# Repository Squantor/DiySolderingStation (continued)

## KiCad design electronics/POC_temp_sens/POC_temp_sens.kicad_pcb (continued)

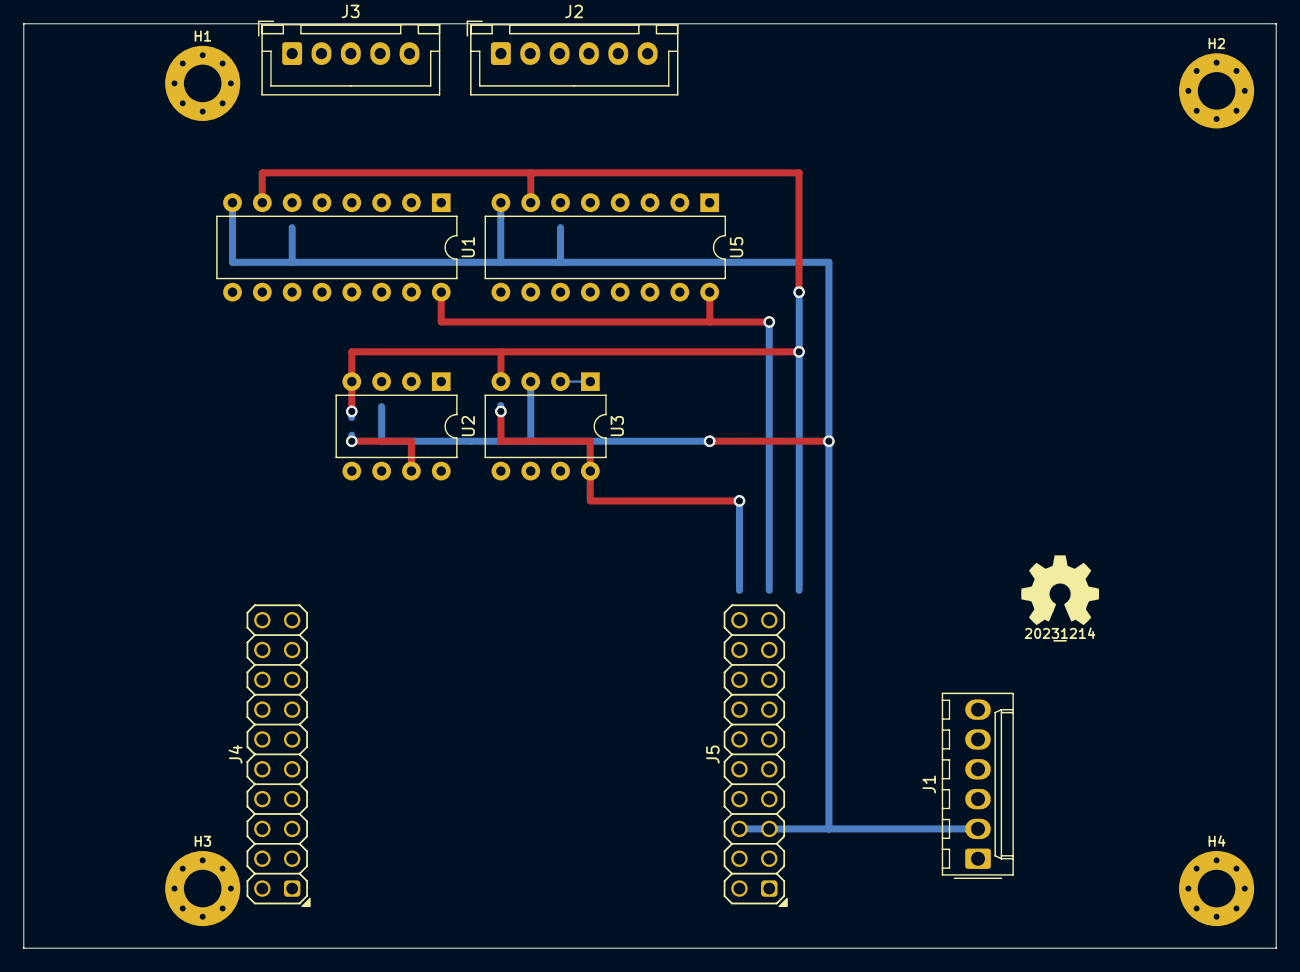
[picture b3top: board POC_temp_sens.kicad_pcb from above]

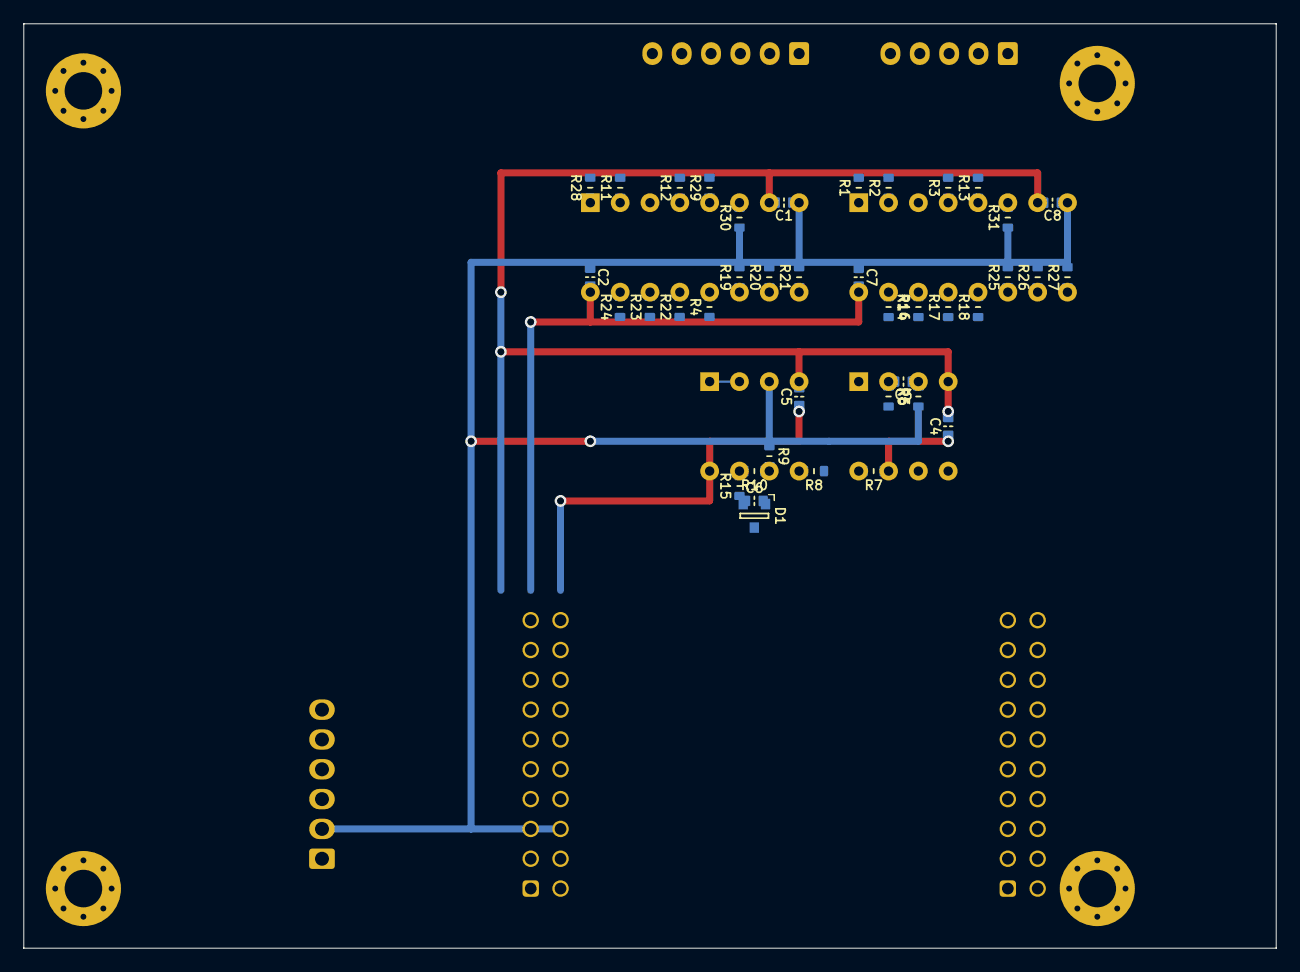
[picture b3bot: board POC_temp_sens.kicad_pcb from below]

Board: 2 copper layers, 106.7 x 78.7 mm, 55 parts (40 on the bottom side), 44 nets.

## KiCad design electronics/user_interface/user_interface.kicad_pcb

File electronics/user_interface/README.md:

# DIY soldering station user interface
User interface for the DIY soldering station consisting of a 2 by 16 character LCD and 4 buttons with a rotary encoder.
## TODO's
* schematic entry
* PCB layout
* Review with one night in between
* Produce at
* Assemble
* Test & characterise
* update Readme.md with pictures and BOM

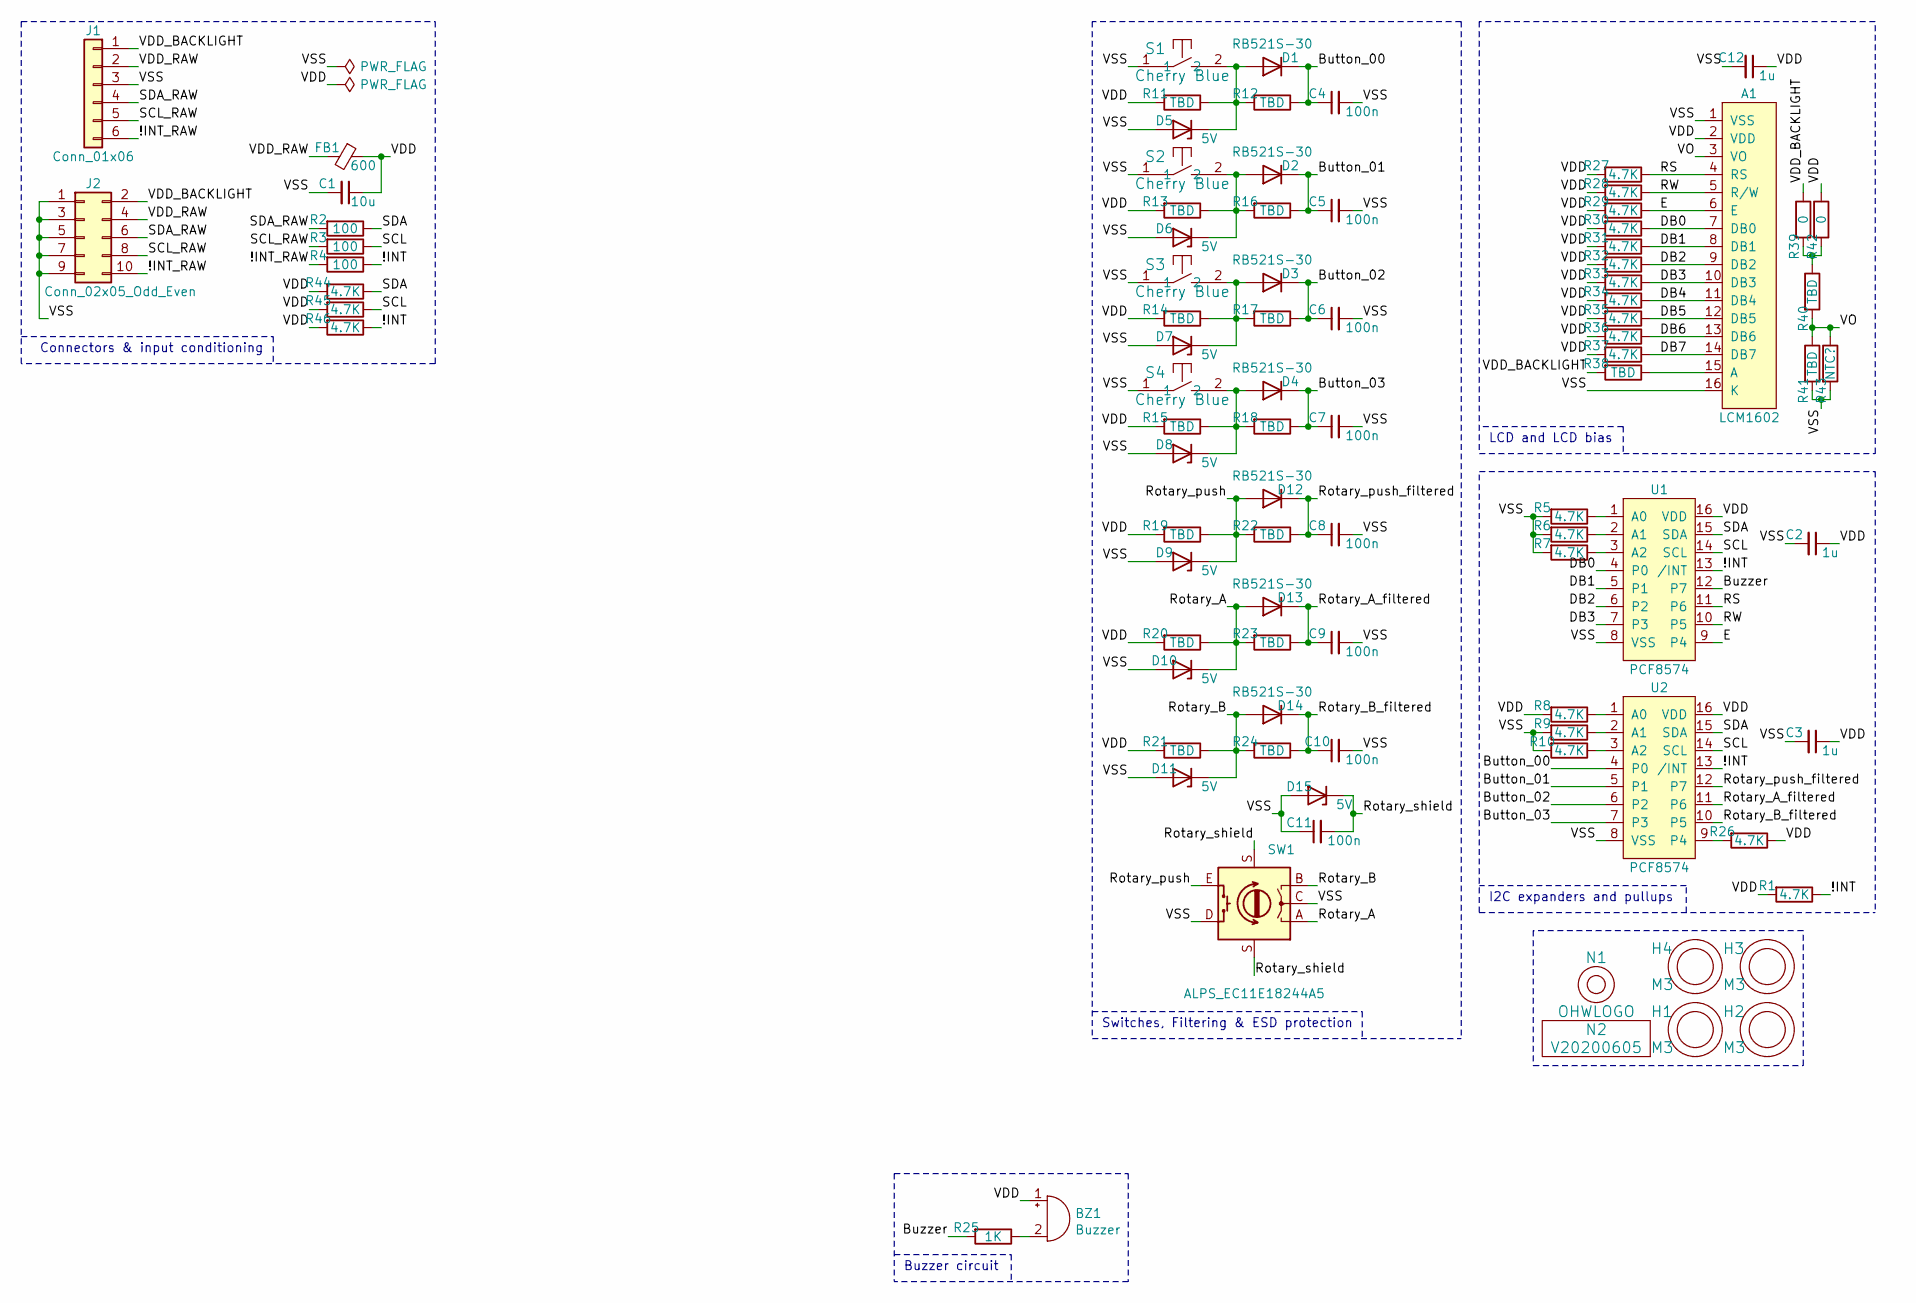
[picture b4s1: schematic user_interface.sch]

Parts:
A1: LCM1602; LCM1602K
BZ1: Buzzer; Buzzer_12x9.5RM7.6
C1: 10u; C_0603
C2, C3, C12: 1u; C_0603
C4, C5, C6, C7, C8, C9, C10, C11: 100n; C_0603
D1, D2, D3, D4, D12, D13, D14: RB521S-30; SOD-523
D5, D6, D7, D8, D9, D10, D11, D15: 5V; SOD-523
FB1: 600; L_0603
H1, H2, H3, H4: M3; MountingHole_3.2mm_M3_Pad_Via
J1: Conn_01x06; JST_PH_S6B-PH-K_1x06_P2.00mm_Horizontal
J2: Conn_02x05_Odd_Even; Header-0254-2X05-H010
N1: OHWLOGO; OSHW-Symbol_6.7x6mm_SilkScreen
N2: V20200605; Label_Generic
R1, R5, R6, R7, R8, R9, R10, R26, R27, R28, R29, R30, R31, R32, R33, R34, R35, R36, R37, R44, R45, R46: 4.7K; R_0603_hand
R2, R3, R4: 100; R_0603_hand
R11, R12, R13, R14, R15, R16, R17, R18, R19, R20, R21, R22, R23, R24, R38, R40, R41: TBD; R_0603_hand
R25: 1K; R_0603_hand
R39, R42: 0; R_0603_hand
R43: NTC?; R_0603_hand
S1, S2, S3, S4: Cherry Blue; MXOnly-1U-NoLED
SW1: ALPS_EC11E18244A5; ALPS_EC11E_style5
U1, U2: PCF8574; SOT162-1-NXP

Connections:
/!INT: R1.1, R4.1, R46.1, U1.13 (/INT), U2.13 (/INT)
/!INT_RAW: J1.6, J2.10, R4.2
/Button_00: C4.1, D1.1 (K), R12.1, U2.4 (P0)
/Button_01: C5.1, D2.1 (K), R16.1, U2.5 (P1)
/Button_02: C6.1, D3.1 (K), R17.1, U2.6 (P2)
/Button_03: C7.1, D4.1 (K), R18.1, U2.7 (P3)
/Buzzer: R25.2, U1.12 (P7)
/DB0: A1.7 (DB0), R30.1, U1.4 (P0)
/DB1: A1.8 (DB1), R31.1, U1.5 (P1)
/DB2: A1.9 (DB2), R32.1, U1.6 (P2)
/DB3: A1.10 (DB3), R33.1, U1.7 (P3)
/DB4: A1.11 (DB4), R34.1
/DB5: A1.12 (DB5), R35.1
/DB6: A1.13 (DB6), R36.1
/DB7: A1.14 (DB7), R37.1
/E: A1.6 (E), R29.1, U1.9 (P4)
/RS: A1.4 (RS), R27.1, U1.11 (P6)
/RW: A1.5 (R/W), R28.1, U1.10 (P5)
/Rotary_A: D10.1 (K), D13.2 (A), R20.1, R23.2, SW1.A
/Rotary_A_filtered: C9.1, D13.1 (K), R23.1, U2.11 (P6)
/Rotary_B: D11.1 (K), D14.2 (A), R21.1, R24.2, SW1.B
/Rotary_B_filtered: C10.1, D14.1 (K), R24.1, U2.10 (P5)
/Rotary_push: D9.1 (K), D12.2 (A), R19.1, R22.2, SW1.E
/Rotary_push_filtered: C8.1, D12.1 (K), R22.1, U2.12 (P7)
/Rotary_shield: C11.2, D15.1 (K), SW1.S (Shield)
/SCL: R3.1, R45.1, U1.14 (SCL), U2.14 (SCL)
/SCL_RAW: J1.5, J2.8, R3.2
/SDA: R2.1, R44.1, U1.15 (SDA), U2.15 (SDA)
/SDA_RAW: J1.4, J2.6, R2.2
/VDD: A1.2 (VDD), BZ1.1 (-), C1.1, C2.1, C3.1, C12.1, FB1.1, R1.2, R8.2, R11.2, R13.2, R14.2, R15.2, R19.2, R20.2, R21.2, R26.1, R27.2, R28.2, R29.2, R30.2, R31.2, R32.2, R33.2, R34.2, R35.2, R36.2, R37.2, R42.1, R44.2, R45.2, R46.2, U1.16 (VDD), U2.16 (VDD)
/VDD_BACKLIGHT: J1.1, J2.2, R38.2, R39.1
/VDD_RAW: FB1.2, J1.2, J2.4
/VO: A1.3 (VO), R40.2, R41.1, R43.1
/VSS: A1.1 (VSS), A1.16 (K), C1.2, C2.2, C3.2, C4.2, C5.2, C6.2, C7.2, C8.2, C9.2, C10.2, C11.1, C12.2, D5.2 (A), D6.2 (A), D7.2 (A), D8.2 (A), D9.2 (A), D10.2 (A), D11.2 (A), D15.2 (A), J1.3, J2.1, J2.3, J2.5, J2.7, J2.9, R5.2, R6.2, R7.2, R9.2, R10.2, R41.2, R43.2, S1.1, S2.1, S3.1, S4.1, SW1.C, SW1.D, U1.8 (VSS), U2.8 (VSS)
unnamed: A1.15 (A), R38.1
unnamed: BZ1.2 (+), R25.1
unnamed: D1.2 (A), D5.1 (K), R11.1, R12.2, S1.2
unnamed: D2.2 (A), D6.1 (K), R13.1, R16.2, S2.2
unnamed: D3.2 (A), D7.1 (K), R14.1, R17.2, S3.2
unnamed: D4.2 (A), D8.1 (K), R15.1, R18.2, S4.2
unnamed: R5.1, U1.1 (A0)
unnamed: R6.1, U1.2 (A1)
unnamed: R7.1, U1.3 (A2)
unnamed: R8.1, U2.1 (A0)
unnamed: R9.1, U2.2 (A1)
unnamed: R10.1, U2.3 (A2)
unnamed: R26.2, U2.9 (P4)
unnamed: R39.2, R40.1, R42.2

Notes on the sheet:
LCD and LCD bias
I2C expanders and pullups
Switches, Filtering & ESD protection
Connectors & input conditioning
Buzzer circuit

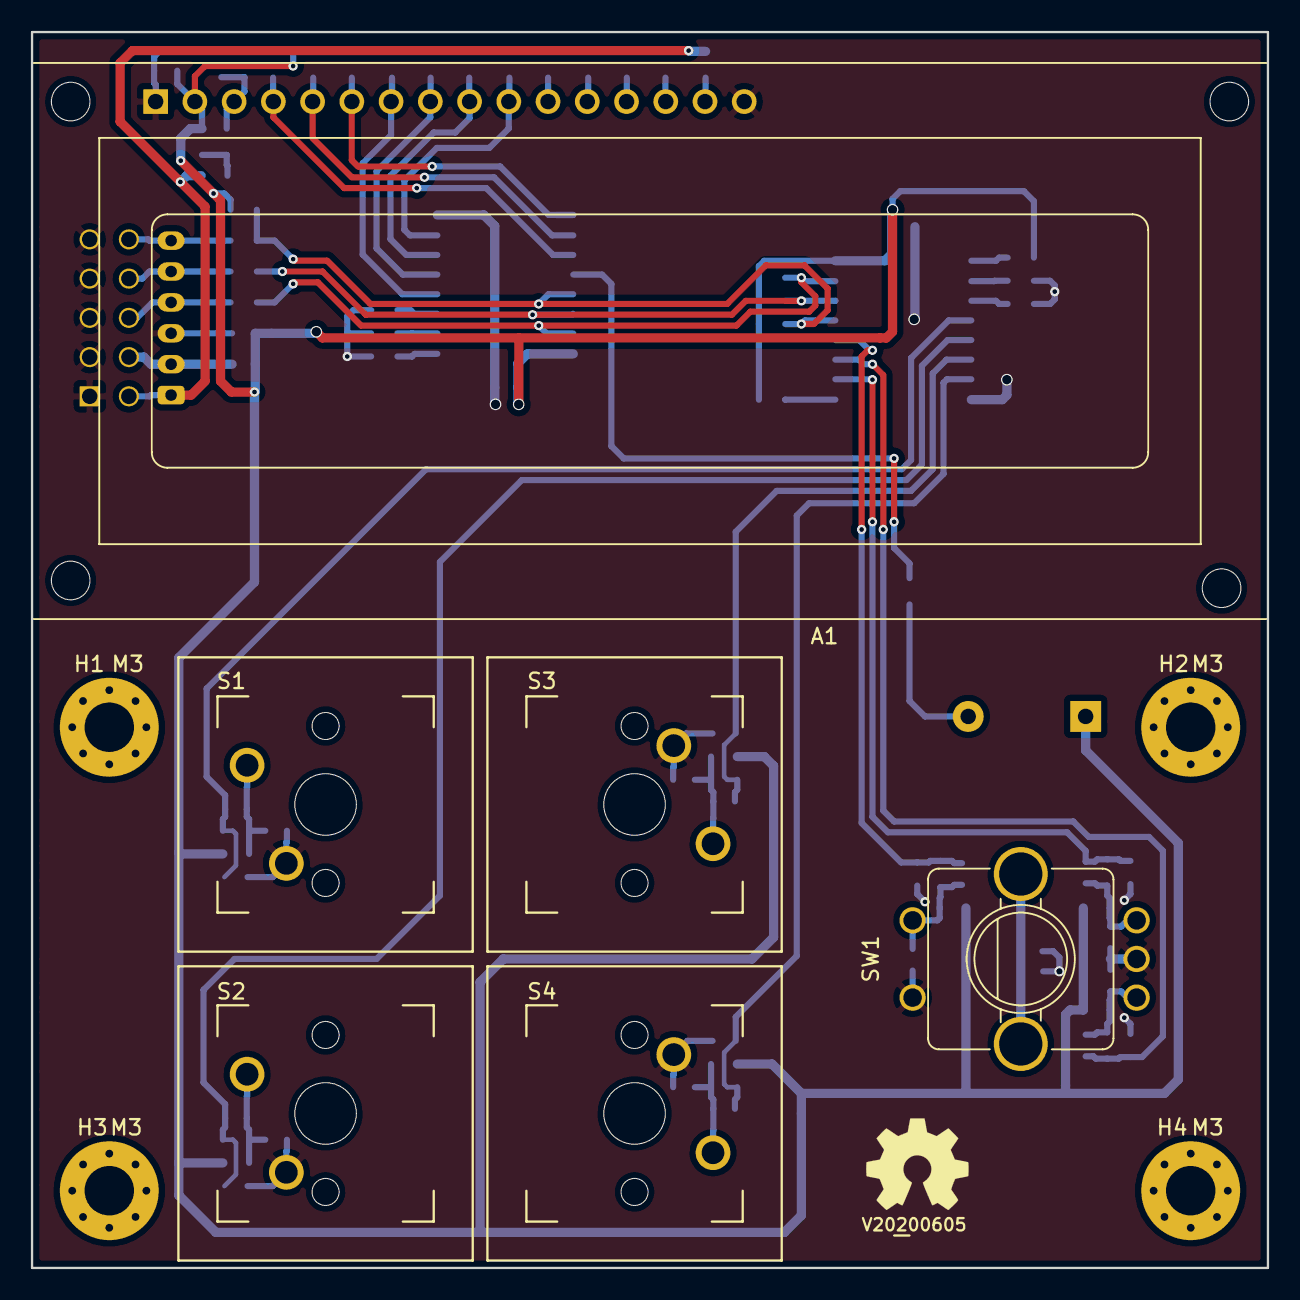
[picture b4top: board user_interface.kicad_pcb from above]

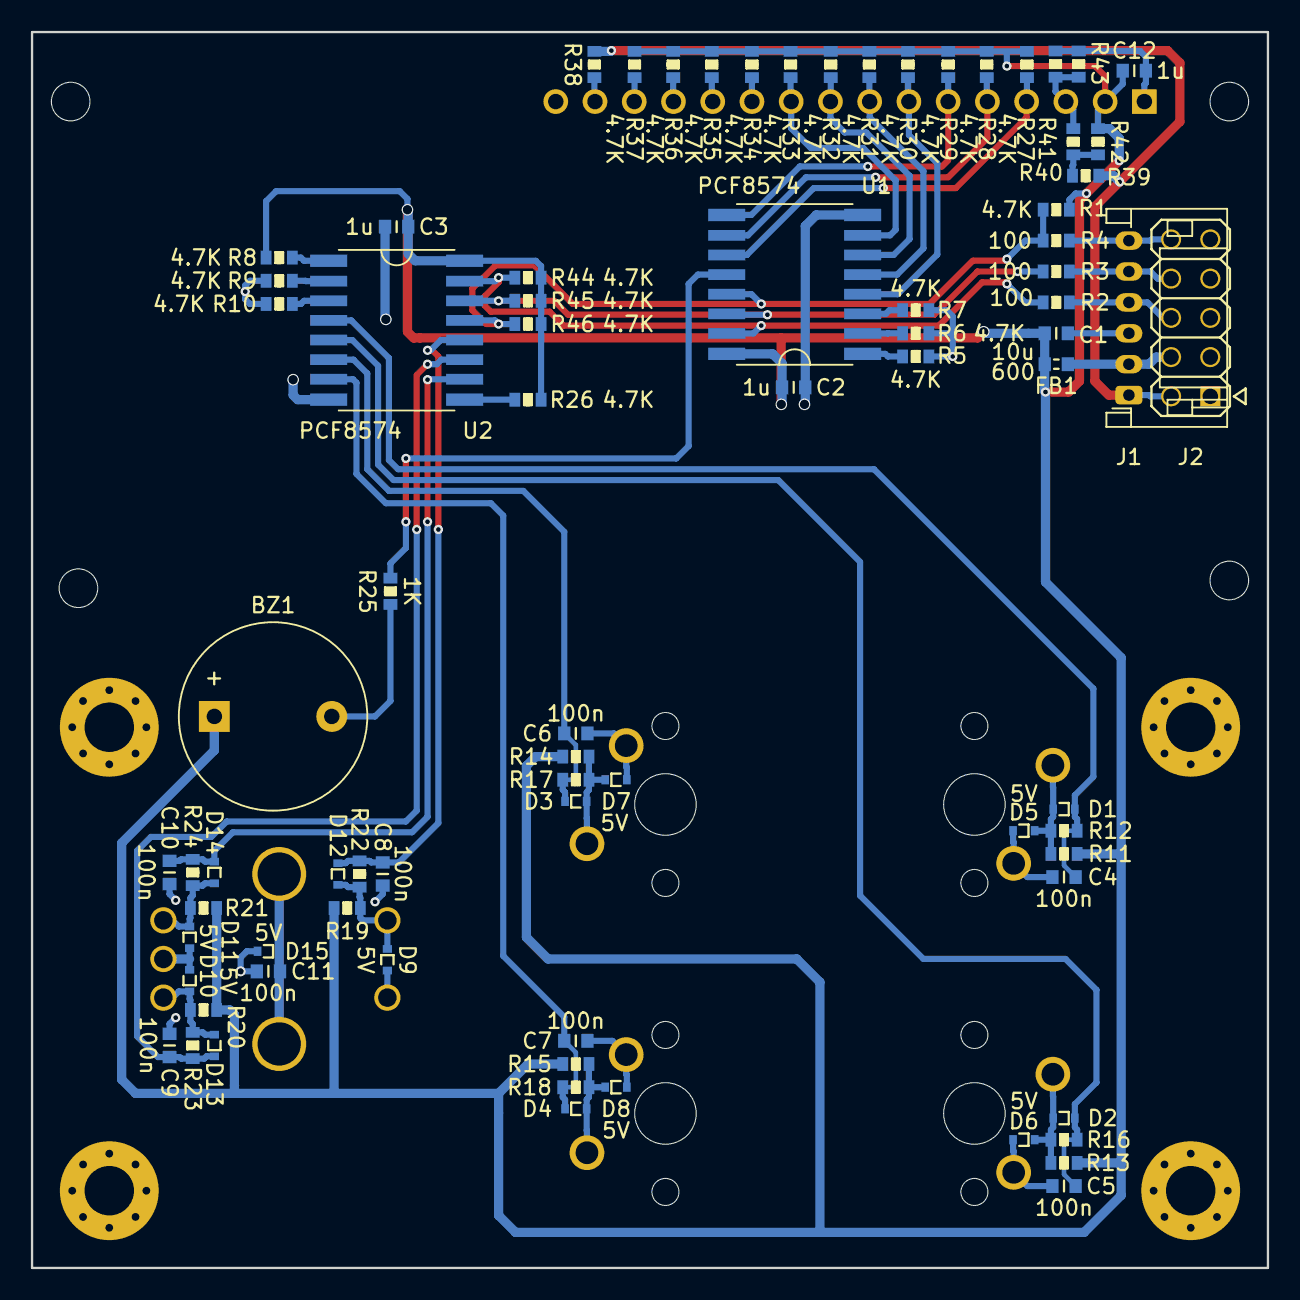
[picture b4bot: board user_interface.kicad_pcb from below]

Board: 2 copper layers, 80.0 x 80.0 mm, 91 parts (79 on the bottom side), 48 nets.

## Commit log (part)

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2020-05-04 typo
2020-05-04 copied over libmcull uart demo project here
2020-05-04 imported a simple time delay library
2020-05-05 split the C bits from the time_delay
2020-05-05 added warning if you did not define a setting
2020-05-05 lets make a delaying class
2020-05-05 updated date on copyright
2020-05-05 added boilerplate stuff
2020-05-05 refactored the systick global increment value
2020-05-05 WIP delay class
2020-05-05 using delay class
2020-05-05 switched to newer C standard
2020-05-05 added time interval class files
2020-05-05 made member const
2020-05-05 added time interval class
2020-05-05 refactored name
2020-05-05 switched to non blocking interval for demo print
2020-05-05 faster builds please
2020-05-06 defined input pin of the zero crossing detector
2020-05-06 started with interrupts on zerocross detector
2020-05-06 working zerocross detection interrupt
2020-05-06 added zerocross counter, seems a bit glitchy...
2020-05-06 enabled hysteresis on pin, much less glitches
2020-05-06 added initial SCR/SSR control scheme
2020-05-07 added SSR control pin
2020-05-07 SSR control demo
2020-05-11 starting with PDM generator
2020-05-11 switched over demo code to separate class
2020-05-11 templated the PDM generator
2020-05-11 added initial projects for the power control and user interface
2020-05-11 added electronics page overview
2020-05-12 processed review comments
2020-05-12 added PCB component library
2020-05-12 added switch library from ai03-2725
2020-05-12 started with user interface schematic entry
2020-05-12 added switch library to user interface project
2020-05-14 power input circuit
2020-05-14 board outline, input circuit layout
2020-05-14 newer PCB library
2020-05-14 ignoring autosave files
2020-05-14 added NXP footprint
2020-05-14 footprints assignment, minor layout positioning
2020-05-14 updated date
2020-05-15 added mounting holes, some silk moves
2020-05-15 minor schematic updates
2020-05-16 added initial switch schematic
2020-05-16 added 3 switches extra to schematic
2020-05-16 minor silk and layout
2020-05-16 added ESD protection
2020-05-16 updated pcb library, included switch libraries
2020-05-16 assigned names to diodes
2020-05-16 rotary encoder now available
2020-05-16 rotary encoder added to schematic WIP components and debouncing
2020-05-16 added rotary encoder knob to PCB
2020-05-17 LCD module now available
2020-05-17 Added LCD, connections to expander and LCD bias circuit
2020-05-17 imported LCD parts, changed board size
2020-05-17 beautified schematic a bit, passes ERC
2020-05-17 mechanical components placed, initial placing of passives
2020-05-17 cache updates
2020-05-19 component placement
2020-05-20 updated footprints to include 3dmodel of SOD-523 diode
2020-05-21 WIP routing of filtering on the buttons
2020-05-21 WIP switch filtering placement and routing, silk changes
2020-05-21 updated versionnumber
2020-05-21 silk placement on filtering done
2020-05-21 WIP LCD parts layout, silk placement, locking UI components (LCD, buttons, etc)
2020-05-21 small updates
2020-05-22 some routing
2020-05-22 added pullup resistors, updated versionnumber
2020-05-22 routing completed
2020-05-22 silk updates
2020-05-24 updated versionnumber, changed address selection tracks so you could disconnect them by cutting traces
2020-05-24 updated to newer cherry mx footprint, changed silk screen of those keys
2020-06-02 added buzzer circuit
2020-06-05 prettyfied the buzzer circuit
2020-06-05 layed out buzzer circuit
2020-06-05 minor silk shifts
2020-06-05 minor silk changes
2024-06-28 updated PCB library
2024-06-28 modifications to newer project structure
2024-06-29 added C14 inlet cutout template and clip
2024-06-30 added wider flange for putting it in case
2024-07-19 added test connector plate for JBC T245 and T115 handle connectors
2024-07-24 added reverse engineered CD-2BC station, going to use some parts from this schematic in this station
2024-07-24 initial start of a CD-2BC T245 thermocouple sensing circuit
2024-07-24 WIP placement
2024-07-24 switched to dual mux for experiments
2024-07-25 switched mux pinning and additional placing
2024-08-02 changed submodule path
2024-08-02 protoboard is now 1 on 1 copy of real protoboard
2024-08-03 reworked firmware structure
2024-08-03 updated mechanical bits documentation
2024-08-03 added more info on mechanical bits
2024-08-04 renaming project and adding some HSI documentation to POC temp sens
2024-08-04 renaming firmware temperature sensing POC
2024-08-04 added unittests
2024-08-04 added application, added systick
2024-08-04 gotten UART loopback working
2024-08-04 started with asynchronous uart hal
2024-08-05 started with synchronous interrupt driven UART HAL
2024-08-05 WIP synchronous interrupt driven UART HAL
2024-08-07 copied ringbuffer to move to libmcu eventually
2024-08-23 uart hal transmit with interrupts work
2024-08-23 added vs code config file garbage
2024-08-23 receive works
2024-08-23 print style functions
2024-08-23 using variadic templates
2024-08-23 added more resistors to multiplexers
2024-08-30 starting with simple commandline
2024-08-30 ported over ansi parser
2024-08-30 added ansi cursor command tests
2024-08-30 starting with creating simple commandline
2024-09-06 method name refactoring
2024-09-06 simple console driver
2024-09-06 console overflow test
2024-09-06 WIP commandline handler
2024-09-06 changed cr/lf handling in commandline, added commandline to POC temp sensing
2024-09-13 initial creation of a simple command handler
2024-09-13 added help function
2024-09-13 started with a command value stack interpreter
2024-09-13 moved ringbuffer to squlib, libmcu will get its own private one
2024-09-13 added some TODO's
2024-09-13 added few common forth primitives, started with parsing a number
2024-09-13 added ascii parsing push
2024-09-13 integrated command interpreter
2024-09-13 refactored result name into results
2024-09-13 split out command handlers
2024-09-13 forwarding numbers to stack
2024-09-13 added additional commands for stack handling
2024-09-13 refactored value stack, fixed command interpreter tests
2024-09-13 fixed negative number handling, added decimal print
2024-09-14 updated HSI with multiplexer pins, power detection pin and ADC sensing pin
2024-09-14 Added number input to help
2024-09-14 merging sparse headers together
2024-09-14 added application state with status command
2024-09-14 properly detects power state
2024-09-16 refactoring by moving some things to libMcu
2024-09-20 separating out buffered and unbuffered console drivers
2024-09-20 WIP merging print into console drivers
2024-09-20 merged print functionality into console
2024-09-20 preparing to convert toascii from struct/class to function templates
2024-09-20 turned toascii into functions
2024-09-20 converted to console.print
2024-09-21 small changes, updated HSI
2024-09-22 added some setting
2024-09-22 started with multiplexer command
2024-09-26 completed multiplexer set command
2024-09-26 updated library bugfix
2024-09-26 updates due to namespace refactoring
2024-09-27 libmcu namespace renames
2024-09-27 ADC works
2024-09-27 added TC readout command
2024-09-28 started with POC temperature control
2024-09-29 added digital supplies and P&R
2024-09-29 added analog powersupply
2024-09-29 added analog supplies, started with nuclone addition
2024-09-30 added nuclone footprint and component
2024-10-02 analog input filtering and post amps, started with diff amps
2024-10-07 synchronized with project template
2024-10-07 finished diff amp schematic and analog multiplexers
2024-10-11 WIP DIY soldering station
2024-10-18 updated to use clocking API
2024-10-25 placed, duplicated power stage
2024-10-25 straggling changes
2024-10-25 added zerocross detector schematic
2024-11-11 replaced current sense resistor, imported zerocross detector
2024-11-15 more schematic bits added, passes ERC, placing components and fixing silk orientations
2024-11-29 some placing and routing done
2024-12-13 further work on place and route, fixed some things with schematic
2025-04-11 WIP further routing
2025-04-18 WIP silk placement
2025-05-02 ignoring some outputs
2025-05-02 updated silk placements and component values
2025-05-04 updated silk placement
2025-05-10 added values to all components
2025-05-13 preparing for production
2025-07-25 builds with newer version of libmcu
2025-07-29 changed/updated component values
2025-08-19 fixing build errors after libmcu update
2025-09-05 porting to newer libcmu API completed
2025-09-05 Updated PCB/Schematic to kicad 9
2025-09-08 Added zerocross detection pin and refactored pin/port/function names to adhere to naming convention
2025-09-08 WIP zero cross detector
2025-09-08 working zero cross interrupt pin
2025-09-09 some refactoring of application object names
2025-09-10 refactoring some names and added zerocrossing class
2025-09-10 added power control pins and functions
2025-09-26 updated library for iocon glitch filter settings, added glitch filtering to Zerocross detector pin
2025-09-26 Initial commit for dual powerstage module
2025-09-26 Schematic and layout done, review needed
2025-10-03 Review completed, fixed DRC warnings
2025-10-03 Started by adding the SH1106 display
2025-10-07 fixed issues with dependency generation
2025-10-10 working display integrated
2025-10-24 WIP asynchronous display handling
2025-11-28 further work on async drivers
2026-01-09 started with button handler
2026-01-09 WIP buttons
2026-01-09 ERC/DRC fixes, headers better aligned
2026-01-17 preparation for production
2026-01-17 added tiled version
2026-01-17 added cut silk lines
2026-06-12 updated to different libmcu API
2026-06-12 porting menu code from playgrounds, naming refactoring, cleanup
2026-06-12 fixed compilation issues
2026-06-19 added power control from zerocross
2026-06-19 fixed a bug with button handler command
2026-06-19 WIP PDM modulator
